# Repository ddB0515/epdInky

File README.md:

# epdInky

ESP32-P4 board for driving RAW E-Ink display panels, epdInky is powered by ESP32-P4 and companion ESP32-C6 for WiFi

If you wanna get one for yourself hop to shop: https://shop.fasani.de/en_US/products/epdinky

# Hardware Specifications

## SoC
- **Model:** Espressif Systems ESP32-P4NRW32

## CPU
- Dual-core 32-bit RISC-V High-Performance (HP) CPU
  - Up to **400 MHz**
  - AI instruction extension
  - Single-precision FPU
- Single-core RISC-V Low-Power (LP) MCU
  - Up to **40 MHz**

## Memory
- 768 KB HP L2MEM (shared by dual-core CPU)
- 32 KB LP SRAM
- 8 KB TCM (for LP MCU core)
- 32 MB PSRAM

## Storage
- **Internal ROM**
  - 128 KB HP ROM
  - 16 KB LP ROM
- **Flash**
  - 32 MB QSPI NOR Flash
- **Expandable**
  - MicroSD card slot

## Graphics & Video
- **GPU:** 2D Pixel Processing Accelerator (PPA)
- **VPU:** H.264 and JPEG codec support

## Camera
- MIPI CSI camera sensor interface

## Wireless
- **Companion chip:** ESP32-C6
- 2.4 GHz Wi-Fi 6
- Bluetooth 5.x Low Energy (LE)
- IEEE 802.15.4 radio
  - Zigbee
  - Thread
  - Matter

## USB
- USB Type-C port
  - Power
  - Debugging

## Sensors
- 6-axis KXTJ3-1057 motion sensor
  - Portrait/landscape orientation detection

## Miscellaneous
- Reset button
- Boot button
- Power LED
- Battery LED
- RV-3028-C7 RTC with timed interrupt wake-up support

## Power Supply
- 5V via USB Type-C
- JST battery connector

## Dimensions
- **100 × 55 mm**

## I2C peripherals:

- TPS651851RSLR - PMIC for e-Ink (I2C addr: 0x68)
- KXTJ3-1057 - 3-axis accelerometar  (I2C addr: 0x0F)
- RV-3028-C7 - RTC (I2C addr: 0x52)
- STC3115AIQT - Fuel guage (I2C addr: 0x70)
- TCA6408ARGTR - GPIO Extender (I2C addr: 0x21)
- TP4056 Battery charger (500mA)

Software side:

Currently examples use [FastEPD](https://github.com/bitbank2/FastEPD/) library and plan is to support
* epdiy
* TRMNL
* HA (custom FW)

List of panels tested and working (keep in mind 2/4bit support for panels is still WIP and will be some time to do it)

| Panel | Resulution | 8/16bit | Gray levels | Pin count | Tested |
| ----- | ---------- | ------- | ----------- | --------- | ------ |
| ED070KH1 | 1680x1264 | 16 bit | 1/2/4 | 40 pin |    1 bit only    |
| ED097TC2 | 1200x825 | 8 bit | 1/2/4 | 33 pin | 1 bit only |
| ES133TT3 | 2200x1650 | 16 bit | 1/2/4 | 39 pin | 1 bit only |
| ED115OC1 | 2760x2070 | 16 bit | 1/2/4 | 40 pin | 1 bit only |
| ED113TC1| 2400x1034 | 16 bit | 1/2/4 | 50 pin | 1 bit only |
| ED052TC4 | 1280x720 | 8 bit | 1/2/4 | 50 pin | 1 bit only |
| ED060SCN | 800x600 | 8 bit| 1/2/4 | 34 pin | 1 bit only |
| ED060SCP | 800x600 | 8 bit| 1/2/4 | 34 pin | 1 bit only |
| ED060SC7 | 800x600 | 8 bit| 1/2/4 | 34 pin | 1 bit only |
| ET017QG1 |320x240| 8 bit | 1/2/4 | 39 pin| 1 bit only |
| ED103TC2 | 1872x1404 | 16 bit | 1/2/4 | 40 pin| 1 bit only |
| ED078KC1 | 1872x1404 | 16 bit | 1/2/4 | 40 pin| 1 bit only |
|       |            |         |             |           |        |
|       |            |         |             |           |        |

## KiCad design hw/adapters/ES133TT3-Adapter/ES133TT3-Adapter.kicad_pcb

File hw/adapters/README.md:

# List of adapters so far that are manufactured and tested

### AllInOneAdapter

This adapter have:<br>
* 40 pin (this is double side contacts) so some panels will need to reverse it (due to opposite pins but works)<br>
* 34 pin (this is double side contacts) so some panels will need to reverse it (due to opposite pins but works)<br>
* 33 pin (bottom side contacts) as didn't find any reverse panels but if do in future can be updated to support it <br>

### AllInOneAdapter-39pin

This adapter have 3 39pin connectors for different models but different style panels could be connected (check schematic)<br>
* ED133UT2<br>
* ED060SC4<br>
* ET107QG1 (U2 on PCB is not populated (for backlight)<br>

### ED052TC4-Adapter

### ED060SC7-Adapter

### ED113TC1-Adapter

### EPD-Adapter
This is generic universal adapter for prototyping when want to have exposed pads (with header ot not) 

### ES133TT3-Adapter

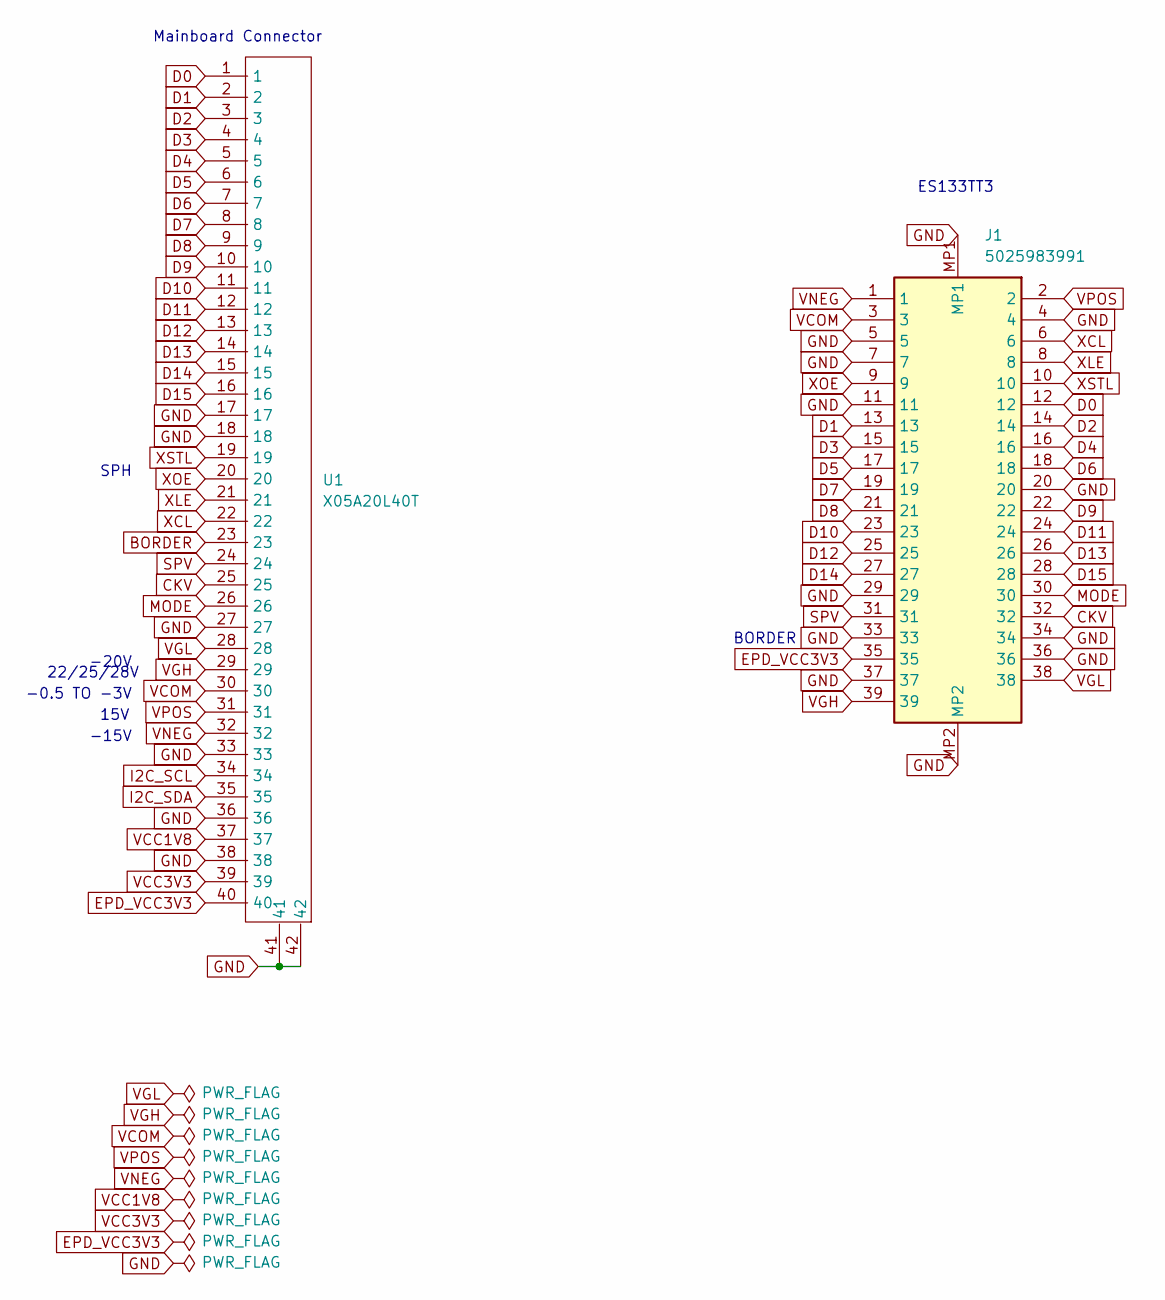
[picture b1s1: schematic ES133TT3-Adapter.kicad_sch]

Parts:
J1: 5025983991; 5025983993; Mouser Part Number 798-FH2639S0.3SHW05
U1: X05A20L40T; X05A20L40T-2

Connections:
BORDER: U1.23
CKV: J1.32, U1.25
D0: J1.12, U1.1
D1: J1.13, U1.2
D2: J1.14, U1.3
D3: J1.15, U1.4
D4: J1.16, U1.5
D5: J1.17, U1.6
D6: J1.18, U1.7
D7: J1.19, U1.8
D8: J1.21, U1.9
D9: J1.22, U1.10
D10: J1.23, U1.11
D11: J1.24, U1.12
D12: J1.25, U1.13
D13: J1.26, U1.14
D14: J1.27, U1.15
D15: J1.28, U1.16
EPD_VCC3V3: J1.35, U1.40
GND: J1.4, J1.5, J1.7, J1.11, J1.20, J1.29, J1.33, J1.34, J1.36, J1.37, J1.MP1, J1.MP2, U1.17, U1.18, U1.27, U1.33, U1.36, U1.38, U1.41, U1.42
I2C_SCL: U1.34
I2C_SDA: U1.35
MODE: J1.30, U1.26
SPV: J1.31, U1.24
VCC1V8: U1.37
VCC3V3: U1.39
VCOM: J1.3, U1.30
VGH: J1.39, U1.29
VGL: J1.38, U1.28
VNEG: J1.1, U1.32
VPOS: J1.2, U1.31
XCL: J1.6, U1.22
XLE: J1.8, U1.21
XOE: J1.9, U1.20
XSTL: J1.10, U1.19

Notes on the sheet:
-20V
SPH
22/25/28V
15V
BORDER
-15V
ES133TT3
Mainboard Connector
-0.5 TO -3V

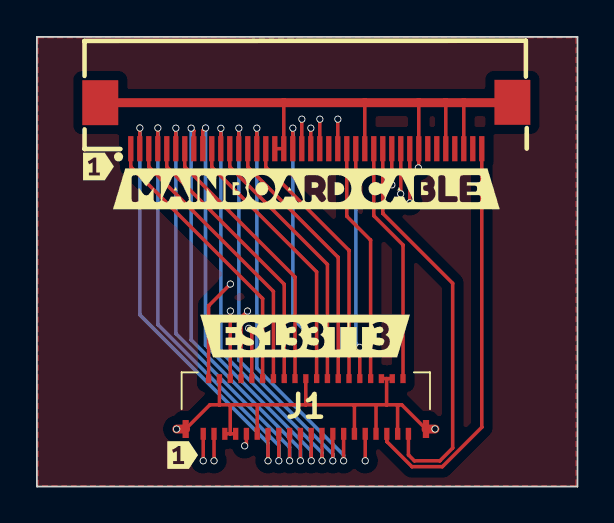
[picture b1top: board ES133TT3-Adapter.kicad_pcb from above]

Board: 4 copper layers, 30.0 x 25.0 mm, 6 parts (0 on the bottom side), 30 nets.

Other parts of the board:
kibuzzard-68DD2F05: G***; kibuzzard-68DD2F05
kibuzzard-68DD142E, kibuzzard-68DD142E#2: G***; kibuzzard-68DD142E
kibuzzard-679CBA1D: G***; kibuzzard-679CBA1D

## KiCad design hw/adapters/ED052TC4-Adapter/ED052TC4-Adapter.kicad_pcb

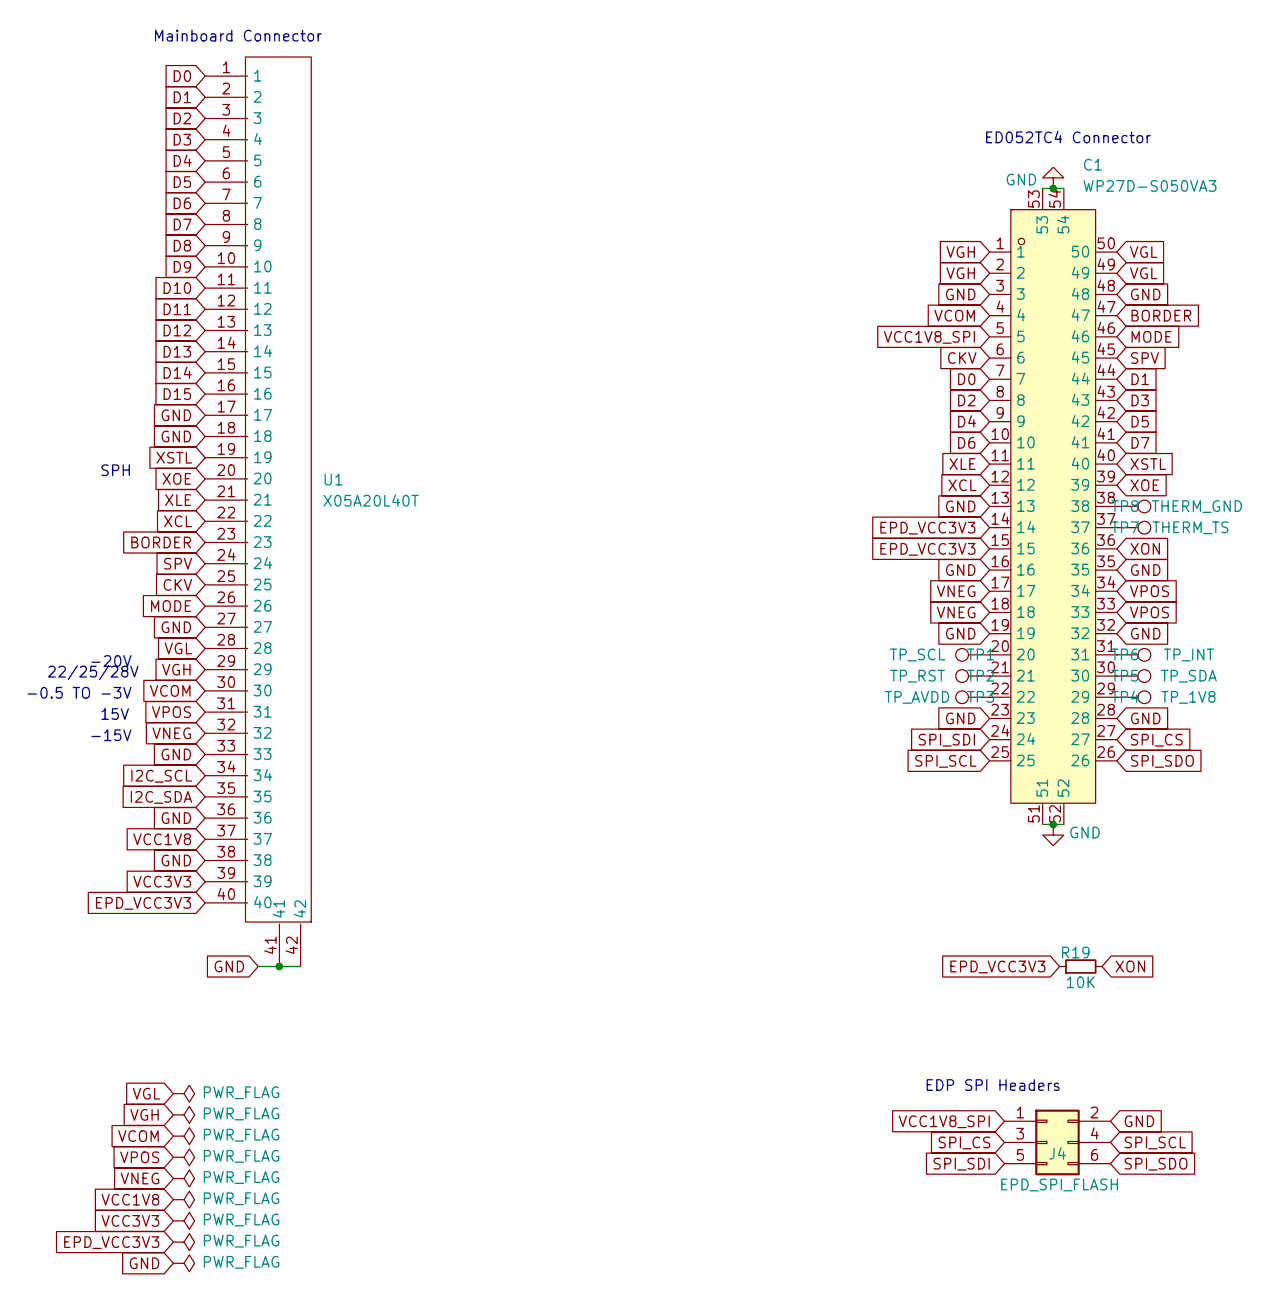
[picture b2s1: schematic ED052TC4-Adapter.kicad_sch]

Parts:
C1: WP27D-S050VA3; LCSC Part C3640690
J4: EPD_SPI_FLASH; PinHeader_2x03_P1.27mm_Vertical
R19: 10K; R_0603_1608Metric
TP1: TP_SCL; TestPoint_Pad_D1.5mm
TP2: TP_RST; TestPoint_Pad_D1.5mm
TP3: TP_AVDD; TestPoint_Pad_D1.5mm
TP4: TP_1V8; TestPoint_Pad_D1.5mm
TP5: TP_SDA; TestPoint_Pad_D1.5mm
TP6: TP_INT; TestPoint_Pad_D1.5mm
TP7: THERM_TS; TestPoint_Pad_D1.5mm
TP8: THERM_GND; TestPoint_Pad_D1.5mm
U1: X05A20L40T; X05A20L40T-2

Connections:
BORDER: C1.47, U1.23
CKV: C1.6, U1.25
D0: C1.7, U1.1
D1: C1.44, U1.2
D2: C1.8, U1.3
D3: C1.43, U1.4
D4: C1.9, U1.5
D5: C1.42, U1.6
D6: C1.10, U1.7
D7: C1.41, U1.8
D8: U1.9
D9: U1.10
D10: U1.11
D11: U1.12
D12: U1.13
D13: U1.14
D14: U1.15
D15: U1.16
EPD_VCC3V3: C1.14, C1.15, R19.1, U1.40
GND: C1.3, C1.13, C1.16, C1.19, C1.23, C1.28, C1.32, C1.35, C1.48, C1.51, C1.52, C1.53, C1.54, J4.2, U1.17, U1.18, U1.27, U1.33, U1.36, U1.38, U1.41, U1.42
I2C_SCL: U1.34
I2C_SDA: U1.35
MODE: C1.46, U1.26
unnamed: C1.20, TP1.1
unnamed: C1.21, TP2.1
unnamed: C1.22, TP3.1
unnamed: C1.29, TP4.1
unnamed: C1.30, TP5.1
unnamed: C1.31, TP6.1
unnamed: C1.37, TP7.1
unnamed: C1.38, TP8.1
SPI_CS: C1.27, J4.3
SPI_SCL: C1.25, J4.4
SPI_SDI: C1.24, J4.5
SPI_SDO: C1.26, J4.6
SPV: C1.45, U1.24
VCC1V8: U1.37
VCC1V8_SPI: C1.5, J4.1
VCC3V3: U1.39
VCOM: C1.4, U1.30
VGH: C1.1, C1.2, U1.29
VGL: C1.49, C1.50, U1.28
VNEG: C1.17, C1.18, U1.32
VPOS: C1.33, C1.34, U1.31
XCL: C1.12, U1.22
XLE: C1.11, U1.21
XOE: C1.39, U1.20
XON: C1.36, R19.2
XSTL: C1.40, U1.19

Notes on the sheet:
ED052TC4 Connector
-20V
SPH
22/25/28V
15V
-15V
Mainboard Connector
EDP SPI Headers
-0.5 TO -3V

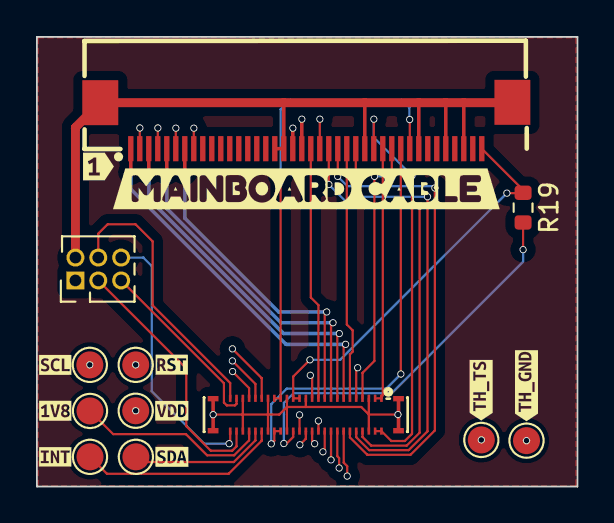
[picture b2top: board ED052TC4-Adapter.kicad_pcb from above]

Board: 4 copper layers, 30.0 x 25.0 mm, 22 parts (0 on the bottom side), 37 nets.

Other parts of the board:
kibuzzard-68DD142E: G***; kibuzzard-68DD142E
kibuzzard-679CBA1D: G***; kibuzzard-679CBA1D
kibuzzard-6992F4CA: G***; kibuzzard-6992F4CA
kibuzzard-6992F4E3: G***; kibuzzard-6992F4E3
kibuzzard-6992F4F4: G***; kibuzzard-6992F4F4
kibuzzard-6992F47A: G***; kibuzzard-6992F47A
kibuzzard-6992F480: G***; kibuzzard-6992F480
kibuzzard-6992F502: G***; kibuzzard-6992F502
kibuzzard-6992F518: G***; kibuzzard-6992F518
kibuzzard-6992F521: G***; kibuzzard-6992F521

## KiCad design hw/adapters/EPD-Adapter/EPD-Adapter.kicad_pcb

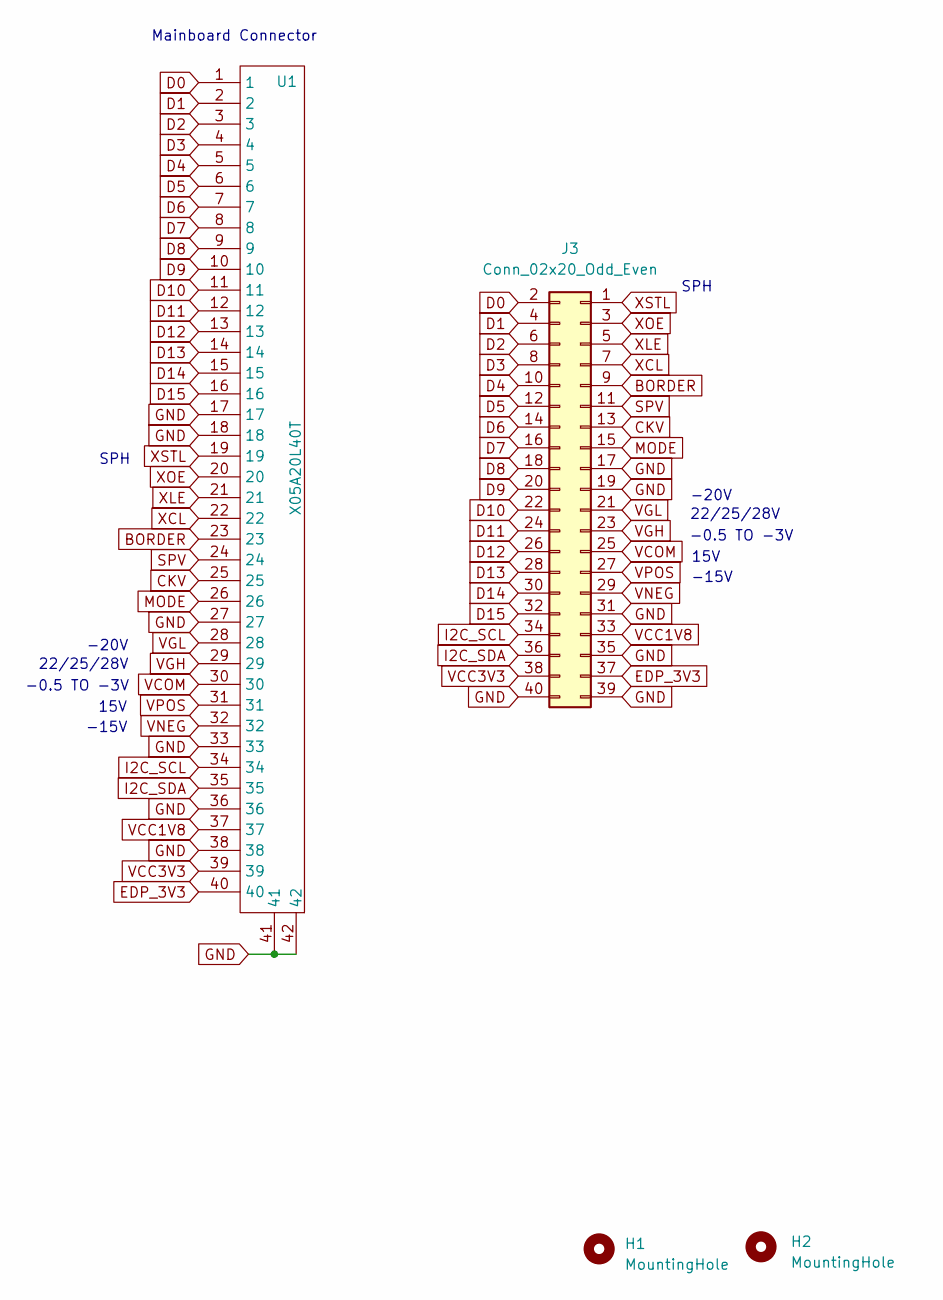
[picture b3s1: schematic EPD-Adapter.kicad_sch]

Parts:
H1, H2: MountingHole; MountingHole_2.2mm_M2_Pad_Via
J3: Conn_02x20_Odd_Even; PinHeader_2x20_P1.27mm_Vertical_SMD
U1: X05A20L40T; X05A20L40T-2

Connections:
BORDER: J3.9, U1.23
CKV: J3.13, U1.25
D0: J3.2, U1.1
D1: J3.4, U1.2
D2: J3.6, U1.3
D3: J3.8, U1.4
D4: J3.10, U1.5
D5: J3.12, U1.6
D6: J3.14, U1.7
D7: J3.16, U1.8
D8: J3.18, U1.9
D9: J3.20, U1.10
D10: J3.22, U1.11
D11: J3.24, U1.12
D12: J3.26, U1.13
D13: J3.28, U1.14
D14: J3.30, U1.15
D15: J3.32, U1.16
EDP_3V3: J3.37, U1.40
GND: J3.17, J3.19, J3.31, J3.35, J3.39, J3.40, U1.17, U1.18, U1.27, U1.33, U1.36, U1.38, U1.41, U1.42
I2C_SCL: J3.34, U1.34
I2C_SDA: J3.36, U1.35
MODE: J3.15, U1.26
SPV: J3.11, U1.24
VCC1V8: J3.33, U1.37
VCC3V3: J3.38, U1.39
VCOM: J3.25, U1.30
VGH: J3.23, U1.29
VGL: J3.21, U1.28
VNEG: J3.29, U1.32
VPOS: J3.27, U1.31
XCL: J3.7, U1.22
XLE: J3.5, U1.21
XOE: J3.3, U1.20
XSTL: J3.1, U1.19

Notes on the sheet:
15V
-0.5 TO -3V
-20V
-15V
22/25/28V
SPH
Mainboard Connector

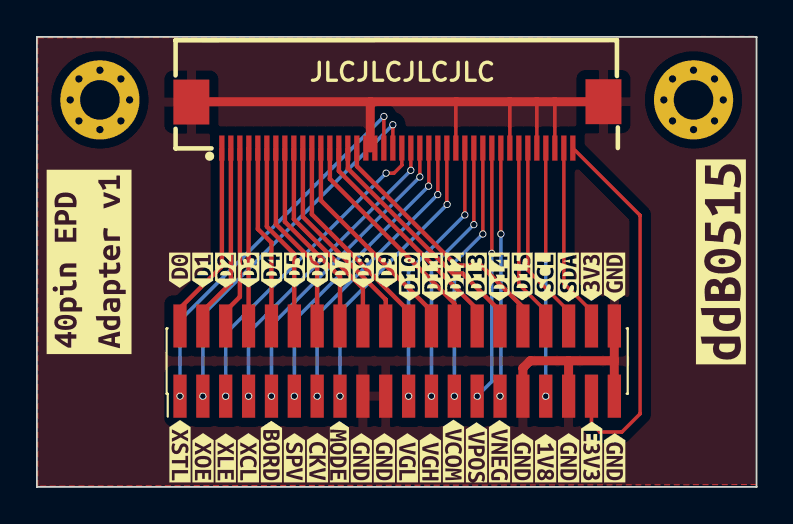
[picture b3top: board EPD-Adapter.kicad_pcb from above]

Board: 2 copper layers, 40.0 x 25.0 mm, 46 parts (0 on the bottom side), 35 nets.

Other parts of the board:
kibuzzard-69C13134: G***; kibuzzard-69C13134
kibuzzard-69D687A5: G***; kibuzzard-69D687A5
kibuzzard-69D687BA: G***; kibuzzard-69D687BA
kibuzzard-69D687C8: G***; kibuzzard-69D687C8
kibuzzard-69D687CF: G***; kibuzzard-69D687CF
kibuzzard-69D687D8: G***; kibuzzard-69D687D8
kibuzzard-69D687E0: G***; kibuzzard-69D687E0
kibuzzard-69D687E9: G***; kibuzzard-69D687E9
kibuzzard-69D687F1: G***; kibuzzard-69D687F1
kibuzzard-69D687F8: G***; kibuzzard-69D687F8
kibuzzard-69D688A1: G***; kibuzzard-69D688A1
kibuzzard-69D688A8: G***; kibuzzard-69D688A8
kibuzzard-69D688AE: G***; kibuzzard-69D688AE
kibuzzard-69D688B2: G***; kibuzzard-69D688B2
kibuzzard-69D688B8: G***; kibuzzard-69D688B8
kibuzzard-69D688BD: G***; kibuzzard-69D688BD
kibuzzard-69D688C3: G***; kibuzzard-69D688C3
kibuzzard-69D688D4: G***; kibuzzard-69D688D4
kibuzzard-69D688DA: G***; kibuzzard-69D688DA
kibuzzard-69D688E1: G***; kibuzzard-69D688E1
kibuzzard-69D688E7: G***; kibuzzard-69D688E7
kibuzzard-69D688ED: G***; kibuzzard-69D688ED
kibuzzard-69D688F3: G***; kibuzzard-69D688F3
kibuzzard-69D6879B: G***; kibuzzard-69D6879B
kibuzzard-69D6880A: G***; kibuzzard-69D6880A
kibuzzard-69D6881E: G***; kibuzzard-69D6881E
kibuzzard-69D6887D: G***; kibuzzard-69D6887D
kibuzzard-69D6888B: G***; kibuzzard-69D6888B
kibuzzard-69D68770: G***; kibuzzard-69D68770
kibuzzard-69D68783: G***; kibuzzard-69D68783
kibuzzard-69D68788: G***; kibuzzard-69D68788
kibuzzard-69D68791: G***; kibuzzard-69D68791
kibuzzard-69D68802: G***; kibuzzard-69D68802
kibuzzard-69D68817: G***; kibuzzard-69D68817
kibuzzard-69D68827: G***; kibuzzard-69D68827
kibuzzard-69D68874: G***; kibuzzard-69D68874
kibuzzard-69D68884: G***; kibuzzard-69D68884
kibuzzard-69D68890: G***; kibuzzard-69D68890
kibuzzard-69D68895: G***; kibuzzard-69D68895
kibuzzard-69FC88FD: G***; kibuzzard-69FC88FD
kibuzzard-69FC895D: G***; kibuzzard-69FC895D
kibuzzard-643538E9: G***; kibuzzard-643538E9

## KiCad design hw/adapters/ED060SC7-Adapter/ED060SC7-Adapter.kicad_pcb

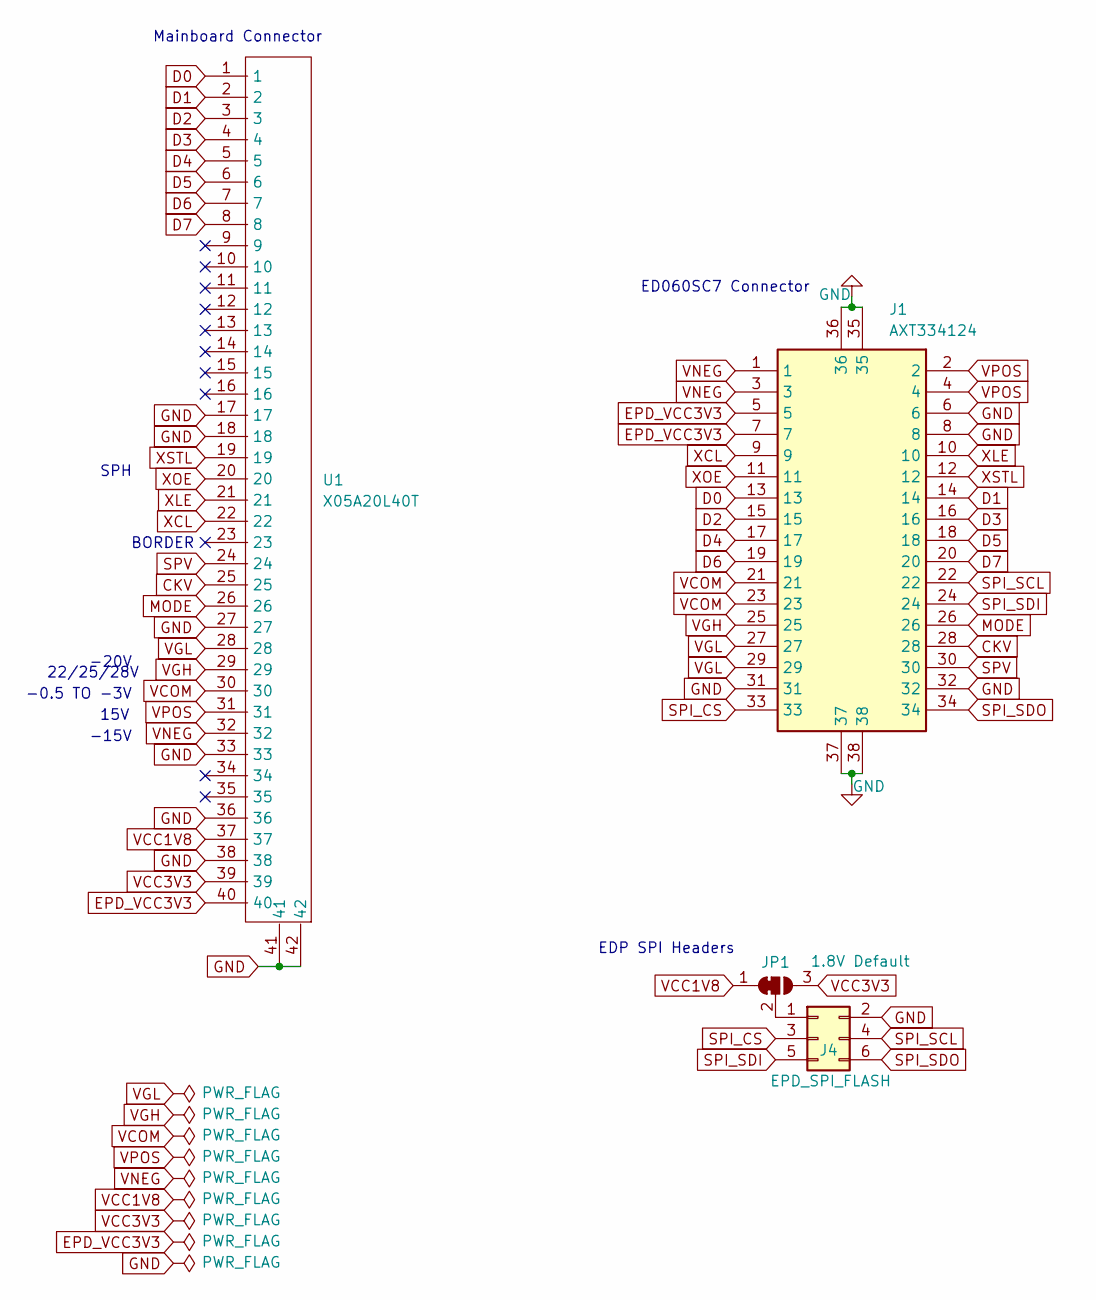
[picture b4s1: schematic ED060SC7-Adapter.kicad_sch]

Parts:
J1: AXT334124
J4: EPD_SPI_FLASH; PinHeader_2x03_P1.27mm_Vertical
JP1: 1.8V Default; SolderJumper-3_P1.3mm_Bridged12_RoundedPad1.0x1.5mm
U1: X05A20L40T; X05A20L40T-2

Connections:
CKV: J1.28, U1.25
D0: J1.13, U1.1
D1: J1.14, U1.2
D2: J1.15, U1.3
D3: J1.16, U1.4
D4: J1.17, U1.5
D5: J1.18, U1.6
D6: J1.19, U1.7
D7: J1.20, U1.8
EPD_VCC3V3: J1.5, J1.7, U1.40
GND: J1.6, J1.8, J1.31, J1.32, J1.35, J1.36, J1.37, J1.38, J4.2, U1.17, U1.18, U1.27, U1.33, U1.36, U1.38, U1.41, U1.42
MODE: J1.26, U1.26
unnamed: J4.1, JP1.2 (C)
SPI_CS: J1.33, J4.3
SPI_SCL: J1.22, J4.4
SPI_SDI: J1.24, J4.5
SPI_SDO: J1.34, J4.6
SPV: J1.30, U1.24
VCC1V8: JP1.1 (A), U1.37
VCC3V3: JP1.3 (B), U1.39
VCOM: J1.21, J1.23, U1.30
VGH: J1.25, U1.29
VGL: J1.27, J1.29, U1.28
VNEG: J1.1, J1.3, U1.32
VPOS: J1.2, J1.4, U1.31
XCL: J1.9, U1.22
XLE: J1.10, U1.21
XOE: J1.11, U1.20
XSTL: J1.12, U1.19

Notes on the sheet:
-20V
SPH
22/25/28V
EDP SPI Headers
15V
-15V
Mainboard Connector
ED060SC7 Connector
BORDER
-0.5 TO -3V

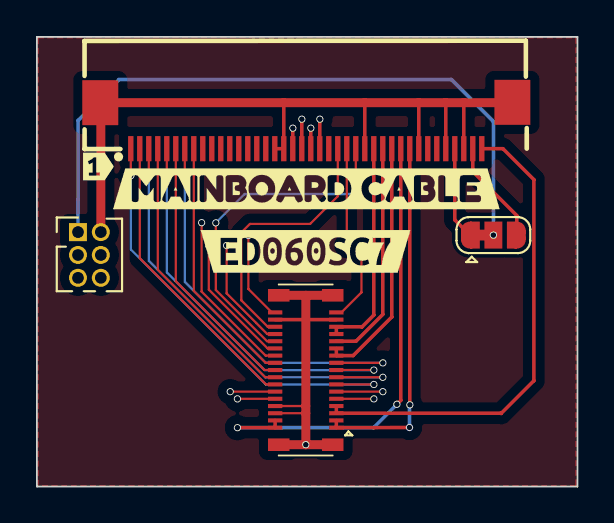
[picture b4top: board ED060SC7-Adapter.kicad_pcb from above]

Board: 4 copper layers, 30.0 x 25.0 mm, 7 parts (0 on the bottom side), 29 nets.

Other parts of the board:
kibuzzard-68DD142E: G***; kibuzzard-68DD142E
kibuzzard-68E910D2: G***; kibuzzard-68E910D2
kibuzzard-679CBA1D: G***; kibuzzard-679CBA1D

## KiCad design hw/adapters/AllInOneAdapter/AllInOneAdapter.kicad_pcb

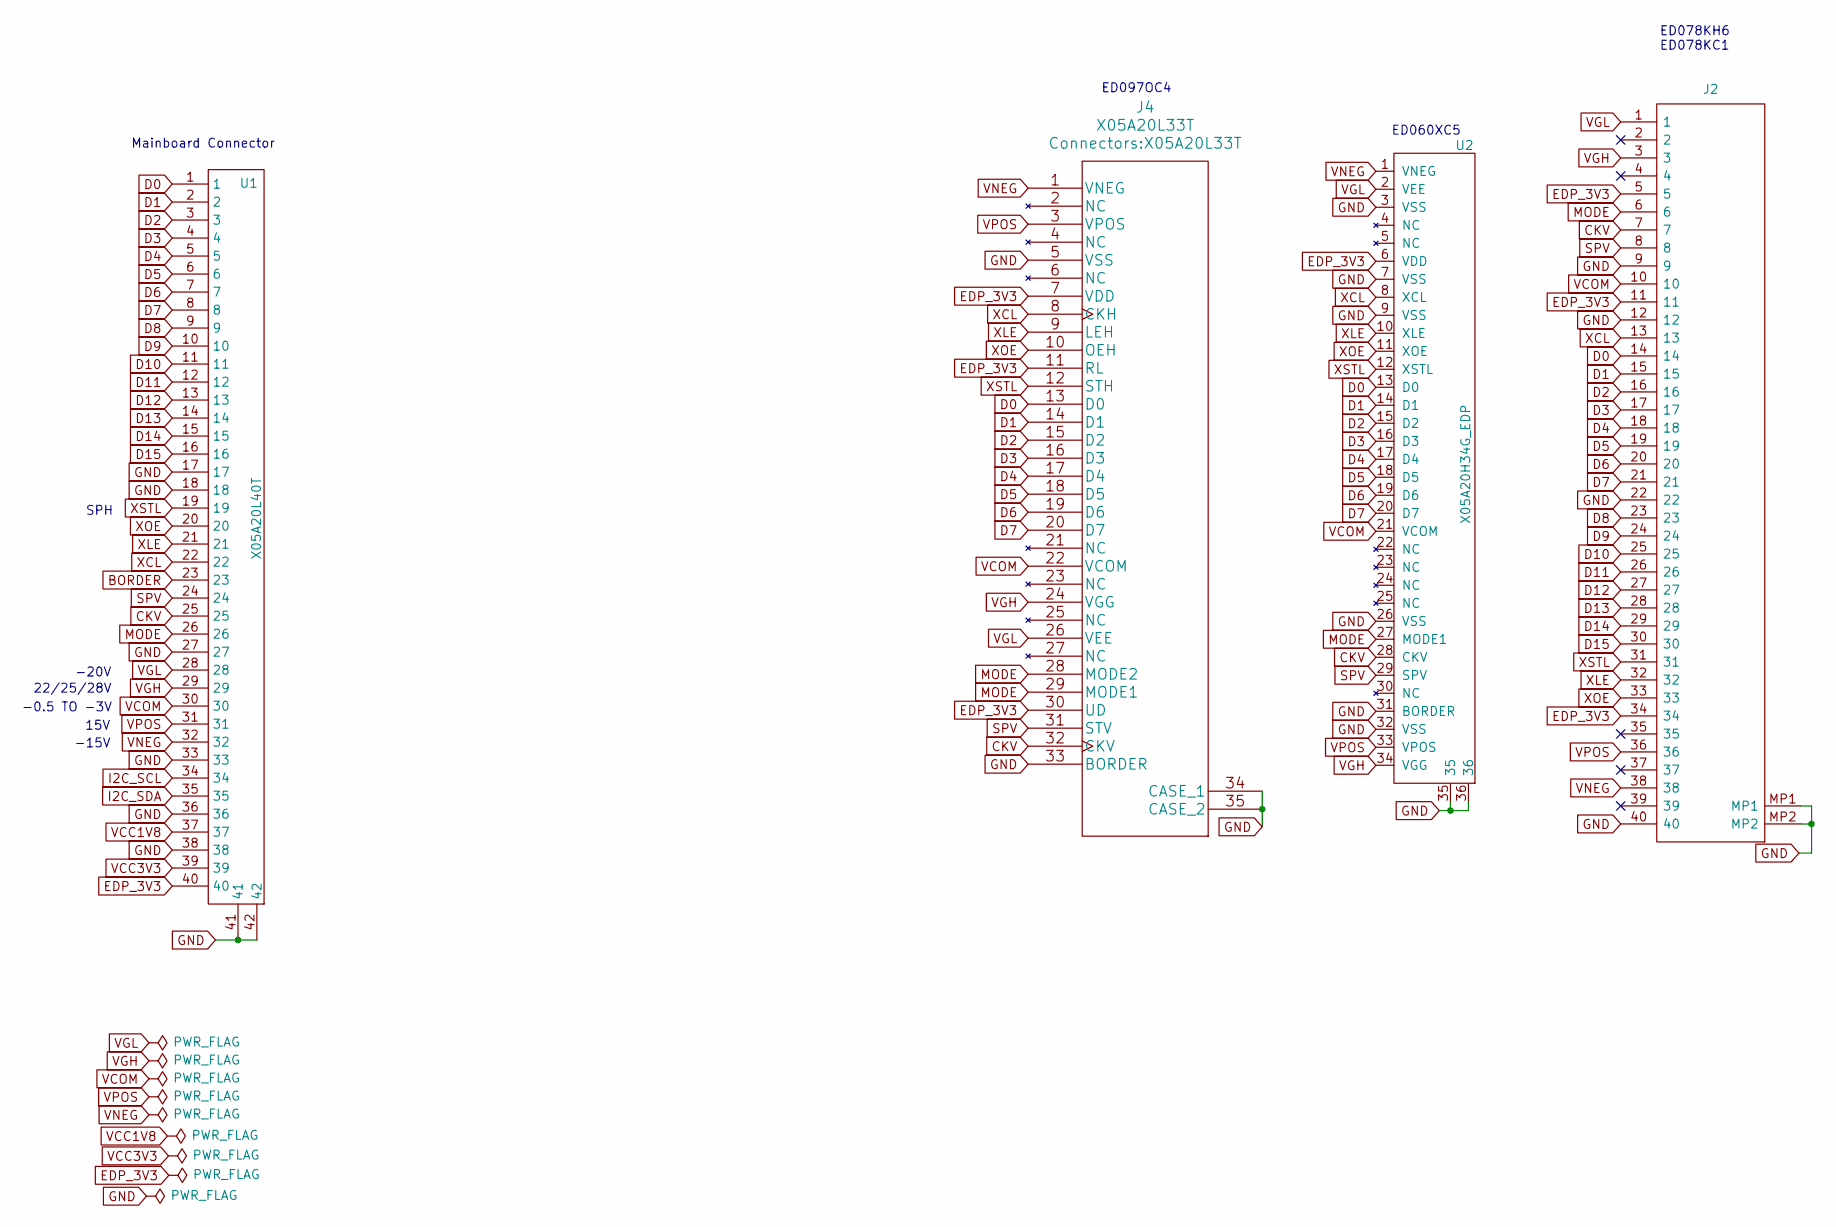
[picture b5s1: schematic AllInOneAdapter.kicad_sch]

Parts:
J2: FH34SRJ-40S-0.5SH; X05A20L40T; Mouser Part Number 798-FH34SRJ40S05SH50
J4: X05A20L33T; LCSC C2880814
U1: X05A20L40T; X05A20L40T-2
U2: X05A20H34G_EDP; X05A20H34G; LCSC C528053

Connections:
BORDER: U1.23
CKV: J2.7, J4.32 (CKV), U1.25, U2.28 (CKV)
D0: J2.14, J4.13 (D0), U1.1, U2.13 (D0)
D1: J2.15, J4.14 (D1), U1.2, U2.14 (D1)
D2: J2.16, J4.15 (D2), U1.3, U2.15 (D2)
D3: J2.17, J4.16 (D3), U1.4, U2.16 (D3)
D4: J2.18, J4.17 (D4), U1.5, U2.17 (D4)
D5: J2.19, J4.18 (D5), U1.6, U2.18 (D5)
D6: J2.20, J4.19 (D6), U1.7, U2.19 (D6)
D7: J2.21, J4.20 (D7), U1.8, U2.20 (D7)
D8: J2.23, U1.9
D9: J2.24, U1.10
D10: J2.25, U1.11
D11: J2.26, U1.12
D12: J2.27, U1.13
D13: J2.28, U1.14
D14: J2.29, U1.15
D15: J2.30, U1.16
EDP_3V3: J2.5, J2.11, J2.34, J4.7 (VDD), J4.11 (RL), J4.30 (UD), U1.40, U2.6 (VDD)
GND: J2.9, J2.12, J2.22, J2.40, J2.MP1, J2.MP2, J4.5 (VSS), J4.33 (BORDER), J4.34 (CASE_1), J4.35 (CASE_2), U1.17, U1.18, U1.27, U1.33, U1.36, U1.38, U1.41, U1.42, U2.3 (VSS), U2.7 (VSS), U2.9 (VSS), U2.26 (VSS), U2.31 (BORDER), U2.32 (VSS), U2.35, U2.36
I2C_SCL: U1.34
I2C_SDA: U1.35
MODE: J2.6, J4.28 (MODE2), J4.29 (MODE1), U1.26, U2.27 (MODE1)
SPV: J2.8, J4.31 (STV), U1.24, U2.29 (SPV)
VCC1V8: U1.37
VCC3V3: U1.39
VCOM: J2.10, J4.22 (VCOM), U1.30, U2.21 (VCOM)
VGH: J2.3, J4.24 (VGG), U1.29, U2.34 (VGG)
VGL: J2.1, J4.26 (VEE), U1.28, U2.2 (VEE)
VNEG: J2.38, J4.1 (VNEG), U1.32, U2.1 (VNEG)
VPOS: J2.36, J4.3 (VPOS), U1.31, U2.33 (VPOS)
XCL: J2.13, J4.8 (CKH), U1.22, U2.8 (XCL)
XLE: J2.32, J4.9 (LEH), U1.21, U2.10 (XLE)
XOE: J2.33, J4.10 (OEH), U1.20, U2.11 (XOE)
XSTL: J2.31, J4.12 (STH), U1.19, U2.12 (XSTL)

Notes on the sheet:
ED060XC5
-20V
ED078KH6 ED078KC1
SPH
22/25/28V
15V
-15V
Mainboard Connector
ED097OC4
-0.5 TO -3V

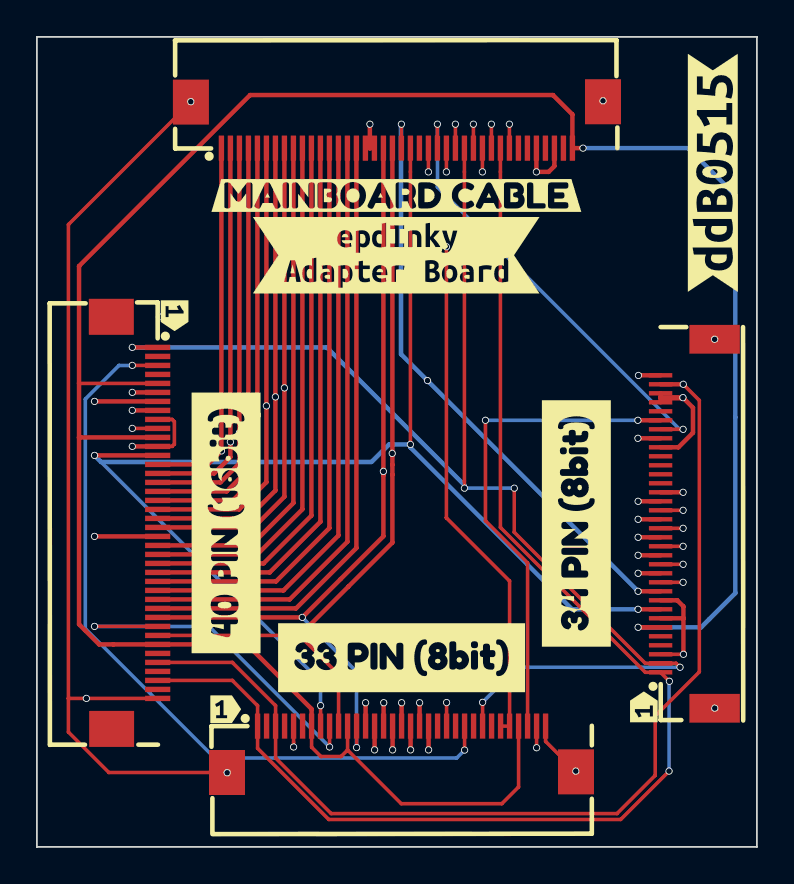
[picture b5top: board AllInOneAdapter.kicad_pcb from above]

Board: 4 copper layers, 40.0 x 45.0 mm, 13 parts (0 on the bottom side), 30 nets.

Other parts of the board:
kibuzzard-64EE76F9: G***; kibuzzard-64EE76F9
kibuzzard-69FC73F9, kibuzzard-69FC73F9#2, kibuzzard-69FC73F9#3: G***; kibuzzard-69FC73F9
kibuzzard-69FC745D: G***; kibuzzard-69FC745D
kibuzzard-69FC7454: G***; kibuzzard-69FC7454
kibuzzard-69FC7469: G***; kibuzzard-69FC7469
kibuzzard-69FC7563: G***; kibuzzard-69FC7563
kibuzzard-655FF6E7: G***; kibuzzard-655FF6E7

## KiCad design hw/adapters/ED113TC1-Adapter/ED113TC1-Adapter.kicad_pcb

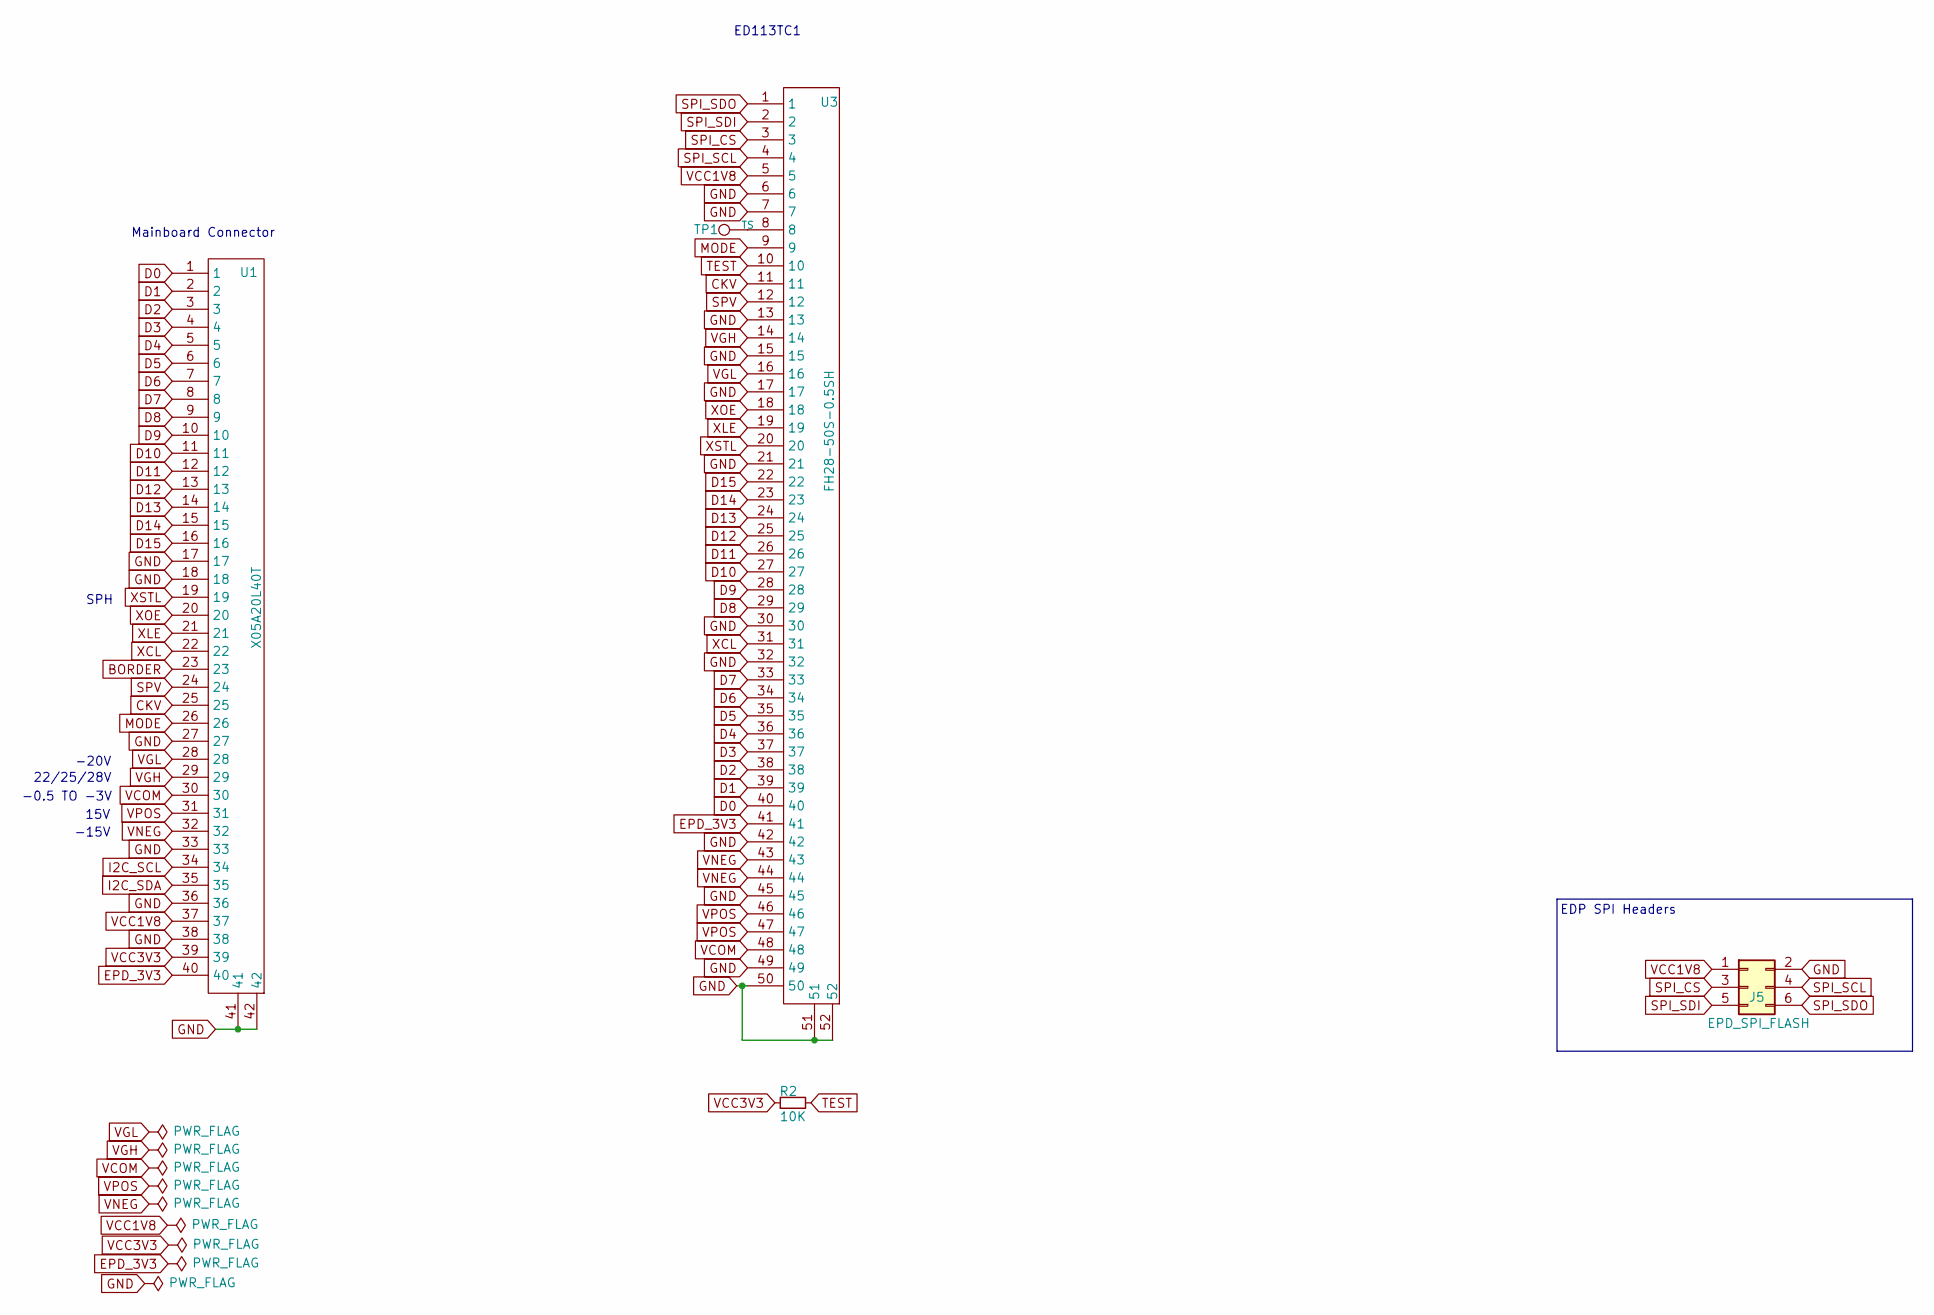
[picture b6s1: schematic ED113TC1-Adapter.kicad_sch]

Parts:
J5: EPD_SPI_FLASH; PinHeader_2x03_P1.27mm_Vertical
R2: 10K; R_0603_1608Metric
TP1: TS; TestPoint_Pad_D1.5mm
U1: X05A20L40T; X05A20L40T-2
U3: FH28-50S-0.5SH

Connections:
BORDER: U1.23
CKV: U1.25, U3.11
D0: U1.1, U3.40
D1: U1.2, U3.39
D2: U1.3, U3.38
D3: U1.4, U3.37
D4: U1.5, U3.36
D5: U1.6, U3.35
D6: U1.7, U3.34
D7: U1.8, U3.33
D8: U1.9, U3.29
D9: U1.10, U3.28
D10: U1.11, U3.27
D11: U1.12, U3.26
D12: U1.13, U3.25
D13: U1.14, U3.24
D14: U1.15, U3.23
D15: U1.16, U3.22
EPD_3V3: U1.40, U3.41
GND: J5.2, U1.17, U1.18, U1.27, U1.33, U1.36, U1.38, U1.41, U1.42, U3.6, U3.7, U3.13, U3.15, U3.17, U3.21, U3.30, U3.32, U3.42, U3.45, U3.49, U3.50, U3.51, U3.52
I2C_SCL: U1.34
I2C_SDA: U1.35
MODE: U1.26, U3.9
unnamed: TP1.1, U3.8
SPI_CS: J5.3, U3.3
SPI_SCL: J5.4, U3.4
SPI_SDI: J5.5, U3.2
SPI_SDO: J5.6, U3.1
SPV: U1.24, U3.12
TEST: R2.2, U3.10
VCC1V8: J5.1, U1.37, U3.5
VCC3V3: R2.1, U1.39
VCOM: U1.30, U3.48
VGH: U1.29, U3.14
VGL: U1.28, U3.16
VNEG: U1.32, U3.43, U3.44
VPOS: U1.31, U3.46, U3.47
XCL: U1.22, U3.31
XLE: U1.21, U3.19
XOE: U1.20, U3.18
XSTL: U1.19, U3.20

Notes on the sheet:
-20V
EDP SPI Headers
SPH
22/25/28V
15V
-15V
Mainboard Connector
ED113TC1
-0.5 TO -3V

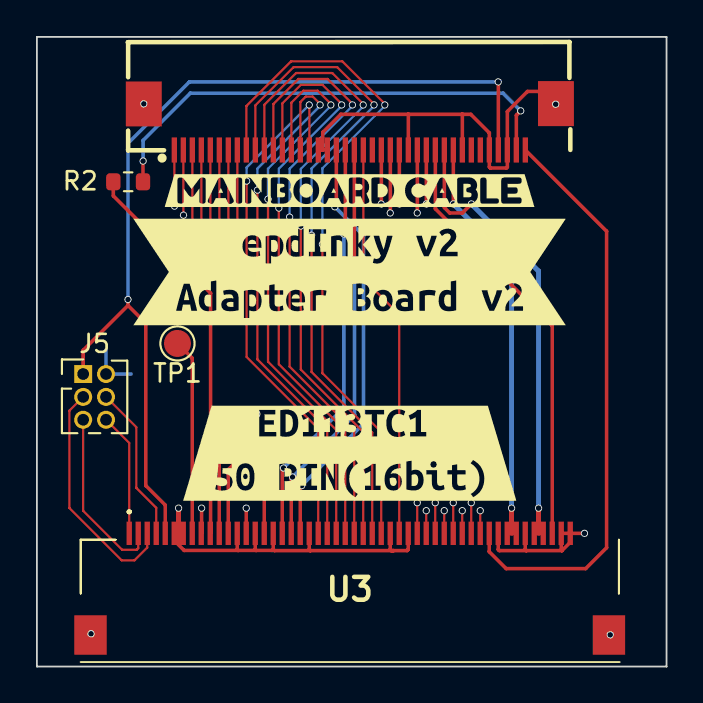
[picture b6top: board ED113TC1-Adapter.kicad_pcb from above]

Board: 4 copper layers, 35.0 x 35.0 mm, 8 parts (0 on the bottom side), 38 nets.

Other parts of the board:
kibuzzard-655FF6E7: G***; kibuzzard-655FF6E7
kibuzzard-65609A2F: G***; kibuzzard-65609A2F
kibuzzard-683734A7: G***; kibuzzard-683734A7
